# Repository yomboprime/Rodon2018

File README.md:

# Rodon2018
Open source wheeled robot.

This project will hold schematics, designs and code for a complete robot.

The robot electronics consist of an SBC (Raspberry-like board) and a Arduino/ESP/STM32-like board.

The main goal of the project is to create software for a wheeled robot suited for a diversity of common controller boards and hardware, i.e. Raspberry-like boards, microcontroller boards, and "Arduino modules". The particular hardware used in the project may differ from yours.

The libre tools used are: Kicad for the electronics, Freecad and Blender for the 3D designs, Inkscape for 2D artwork, and your favourite manner of editing code.

## Documentation

Please read the [project documentation](doc/1_DocumentationMain.md)

## Project phases history

- ✔️ Design MicrocontrollerBoard: Kicad design for the microcontroller board (Atmega1284P-PU)
- ➡️ Ordering and waiting for PCB arrival.
- Test MicrocontrollerBoard with motors.
- Do code a basic software & firmware.
- Keep growing functionality

## Acknowledgements

The small Lidar sensor code is based on the Adafruit VL53L0X Library, which is also MIT Licensed:

### Adafruit VL53L0X Library 

This is a library for the Adafruit VL53L0X time-of-flight breakout:
  * https://www.adafruit.com/products/3317
 
Check out the links above for our tutorials and wiring diagrams. This chip uses I2C to communicate

Adafruit invests time and resources providing this open source code, please support Adafruit and open-source hardware by purchasing products from Adafruit!

Written by Limor Fried/Ladyada for Adafruit Industries.
MIT license, all text above must be included in any redistribution

## License

MIT Licensed, see LICENSE file.

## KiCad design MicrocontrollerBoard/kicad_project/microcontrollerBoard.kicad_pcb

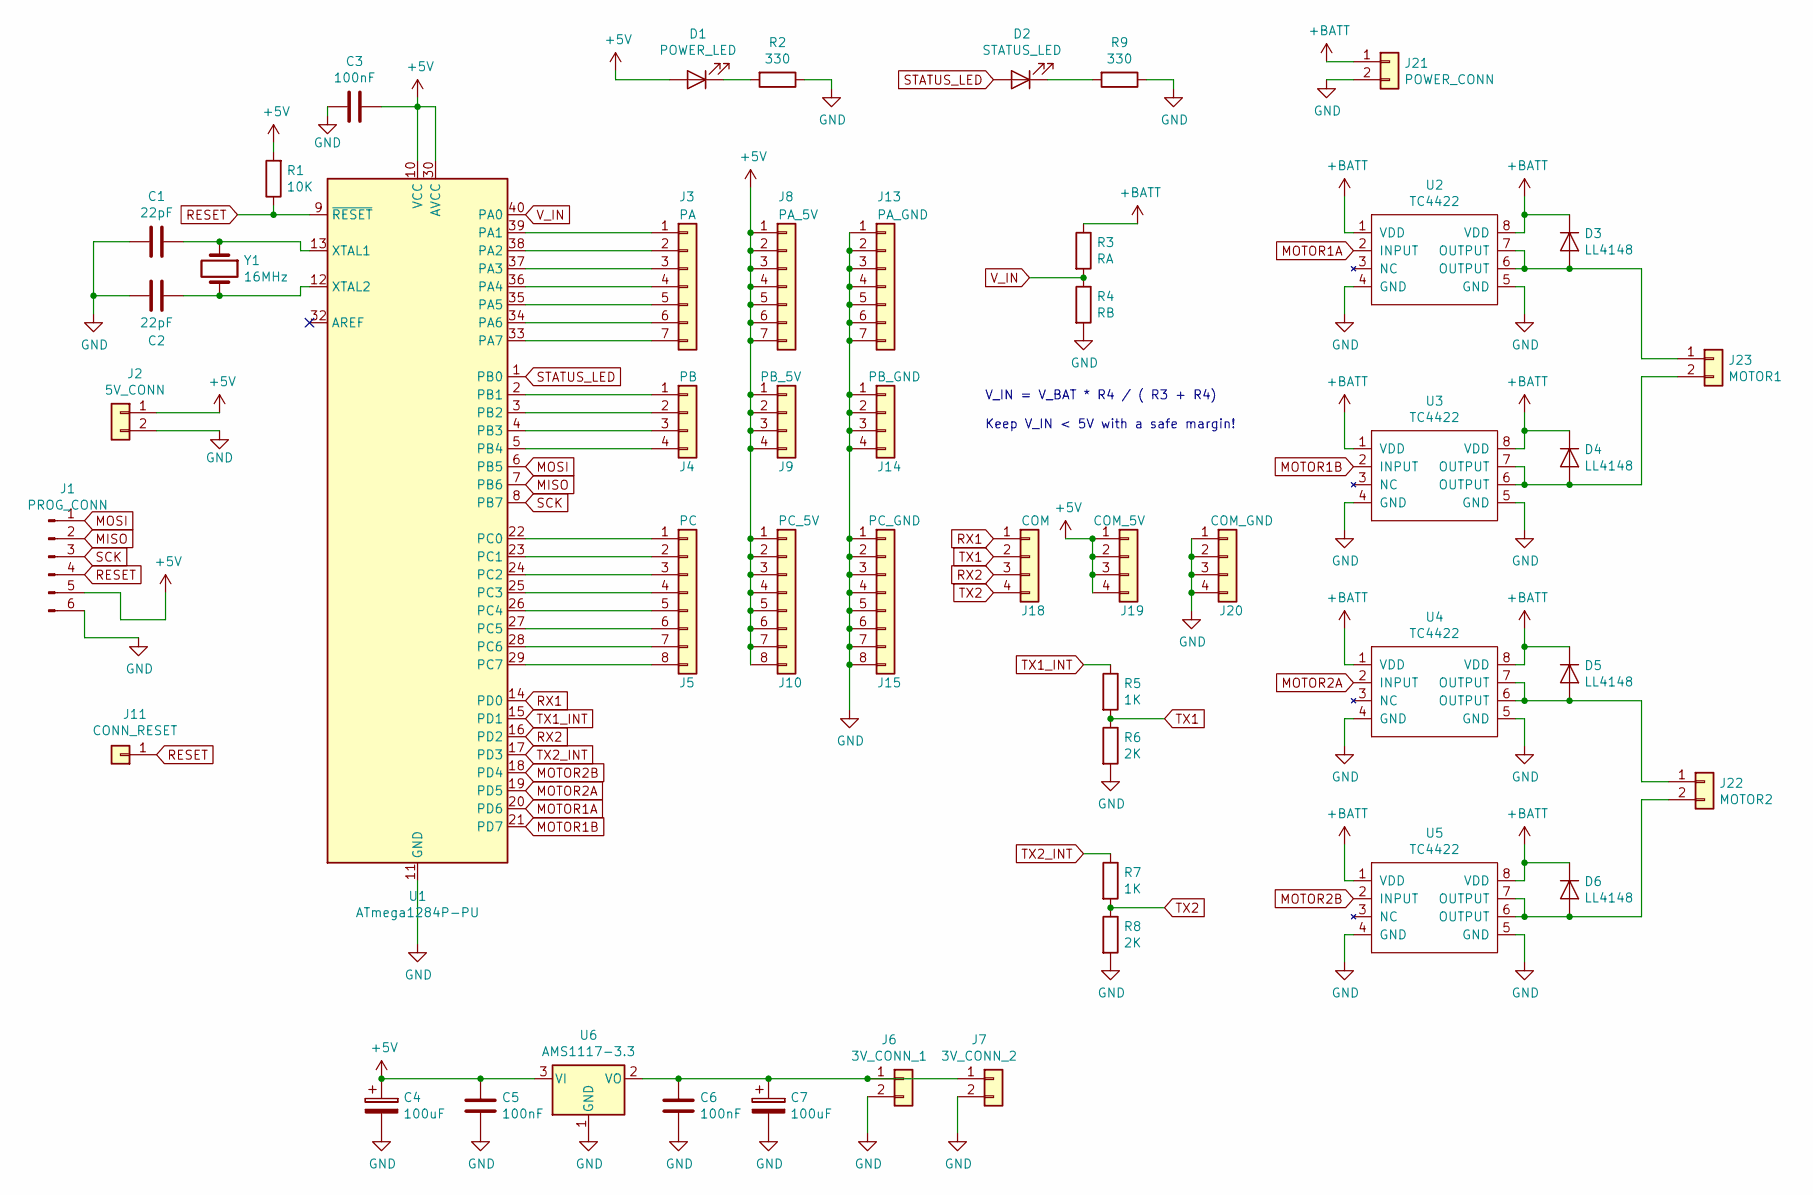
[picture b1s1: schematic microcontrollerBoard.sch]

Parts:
C1, C2: 22pF; C_0805_2012Metric_Pad1.15x1.40mm_HandSolder
C3: 100nF; C_0805_2012Metric_Pad1.15x1.40mm_HandSolder
C4, C7: 100uF; CP_Radial_D5.0mm_P2.50mm
C5, C6: 100nF; C_0603_1608Metric_Pad1.05x0.95mm_HandSolder
D1: POWER_LED; D_0805_2012Metric_Pad1.15x1.40mm_HandSolder
D2: STATUS_LED; D_0805_2012Metric_Pad1.15x1.40mm_HandSolder
D3, D4, D5, D6: LL4148; D_SOD-110
J1: PROG_CONN; PinHeader_1x06_P2.54mm_Vertical
J2: 5V_CONN; PinHeader_1x02_P2.54mm_Vertical
J3: PA; PinHeader_1x07_P2.54mm_Vertical
J4: PB; PinHeader_1x04_P2.54mm_Vertical
J5: PC; PinHeader_1x08_P2.54mm_Vertical
J6: 3V_CONN_1; PinHeader_1x02_P2.54mm_Vertical
J7: 3V_CONN_2; PinHeader_1x02_P2.54mm_Vertical
J8: PA_5V; PinHeader_1x07_P2.54mm_Vertical
J9: PB_5V; PinHeader_1x04_P2.54mm_Vertical
J10: PC_5V; PinHeader_1x08_P2.54mm_Vertical
J11: CONN_RESET; PinHeader_1x01_P2.54mm_Vertical
J13: PA_GND; PinHeader_1x07_P2.54mm_Vertical
J14: PB_GND; PinHeader_1x04_P2.54mm_Vertical
J15: PC_GND; PinHeader_1x08_P2.54mm_Vertical
J18: COM; PinHeader_1x04_P2.54mm_Vertical
J19: COM_5V; PinHeader_1x04_P2.54mm_Vertical
J20: COM_GND; PinHeader_1x04_P2.54mm_Vertical
J21: POWER_CONN; PinHeader_1x02_P2.54mm_Vertical
J22: MOTOR2; PinHeader_1x02_P2.54mm_Vertical
J23: MOTOR1; PinHeader_1x02_P2.54mm_Vertical
R1: 10K; R_0805_2012Metric_Pad1.15x1.40mm_HandSolder
R2, R9: 330; R_0805_2012Metric_Pad1.15x1.40mm_HandSolder
R3: RA; R_0805_2012Metric_Pad1.15x1.40mm_HandSolder
R4: RB; R_0805_2012Metric_Pad1.15x1.40mm_HandSolder
R5, R7: 1K; R_0805_2012Metric_Pad1.15x1.40mm_HandSolder
R6, R8: 2K; R_0805_2012Metric_Pad1.15x1.40mm_HandSolder
U1: ATmega1284P-PU; DIP-40_W15.24mm
U2, U3, U4, U5: TC4422; DIP-8_W7.62mm_Socket_LongPads
U6: AMS1117-3.3; SOT-223-3_TabPin2
Y1: 16MHz; Crystal_HC49-U_Vertical

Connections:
+5V: C3.1, C4.1, C5.1, D1.2 (A), J1.5, J2.1, J8.1, J8.2, J8.3, J8.4, J8.5, J8.6, J8.7, J9.1, J9.2, J9.3, J9.4, J10.1, J10.2, J10.3, J10.4, J10.5, J10.6, J10.7, J10.8, J19.1, J19.2, J19.3, J19.4, R1.2, U1.10 (VCC), U1.30 (AVCC), U6.3 (VI)
+BATT: D3.1 (K), D4.1 (K), D5.1 (K), D6.1 (K), J21.1, R3.1, U2.1 (VDD), U2.8 (VDD), U3.1 (VDD), U3.8 (VDD), U4.1 (VDD), U4.8 (VDD), U5.1 (VDD), U5.8 (VDD)
GND: C1.2, C2.2, C3.2, C4.2, C5.2, C6.2, C7.2, J1.6, J2.2, J6.2, J7.2, J13.1, J13.2, J13.3, J13.4, J13.5, J13.6, J13.7, J14.1, J14.2, J14.3, J14.4, J15.1, J15.2, J15.3, J15.4, J15.5, J15.6, J15.7, J15.8, J20.1, J20.2, J20.3, J20.4, J21.2, R2.1, R4.2, R6.2, R8.2, R9.1, U1.11 (GND), U1.31 (GND), U2.4 (GND), U2.5 (GND), U3.4 (GND), U3.5 (GND), U4.4 (GND), U4.5 (GND), U5.4 (GND), U5.5 (GND), U6.1 (GND)
MISO: J1.2, U1.7 (PB6)
MOSI: J1.1, U1.6 (PB5)
MOTOR1A: U1.20 (PD6), U2.2 (INPUT)
MOTOR1B: U1.21 (PD7), U3.2 (INPUT)
MOTOR2A: U1.19 (PD5), U4.2 (INPUT)
MOTOR2B: U1.18 (PD4), U5.2 (INPUT)
unnamed: C1.1, U1.13 (XTAL1), Y1.1
unnamed: C2.1, U1.12 (XTAL2), Y1.2
unnamed: C6.1, C7.1, J6.1, J7.1, U6.2 (VO)
unnamed: D1.1 (K), R2.2
unnamed: D2.1 (K), R9.2
unnamed: D3.2 (A), J23.1, U2.6 (OUTPUT), U2.7 (OUTPUT)
unnamed: D4.2 (A), J23.2, U3.6 (OUTPUT), U3.7 (OUTPUT)
unnamed: D5.2 (A), J22.1, U4.6 (OUTPUT), U4.7 (OUTPUT)
unnamed: D6.2 (A), J22.2, U5.6 (OUTPUT), U5.7 (OUTPUT)
unnamed: J3.1, U1.39 (PA1)
unnamed: J3.2, U1.38 (PA2)
unnamed: J3.3, U1.37 (PA3)
unnamed: J3.4, U1.36 (PA4)
unnamed: J3.5, U1.35 (PA5)
unnamed: J3.6, U1.34 (PA6)
unnamed: J3.7, U1.33 (PA7)
unnamed: J4.1, U1.2 (PB1)
unnamed: J4.2, U1.3 (PB2)
unnamed: J4.3, U1.4 (PB3)
unnamed: J4.4, U1.5 (PB4)
unnamed: J5.1, U1.22 (PC0)
unnamed: J5.2, U1.23 (PC1)
unnamed: J5.3, U1.24 (PC2)
unnamed: J5.4, U1.25 (PC3)
unnamed: J5.5, U1.26 (PC4)
unnamed: J5.6, U1.27 (PC5)
unnamed: J5.7, U1.28 (PC6)
unnamed: J5.8, U1.29 (PC7)
RESET: J1.4, J11.1, R1.1, U1.9 (~RESET)
RX1: J18.1, U1.14 (PD0)
RX2: J18.3, U1.16 (PD2)
SCK: J1.3, U1.8 (PB7)
STATUS_LED: D2.2 (A), U1.1 (PB0)
TX1: J18.2, R5.2, R6.1
TX1_INT: R5.1, U1.15 (PD1)
TX2: J18.4, R7.2, R8.1
TX2_INT: R7.1, U1.17 (PD3)
V_IN: R3.2, R4.1, U1.40 (PA0)

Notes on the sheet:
V_IN = V_BAT * R4 / ( R3 + R4) Keep V_IN < 5V with a safe margin!

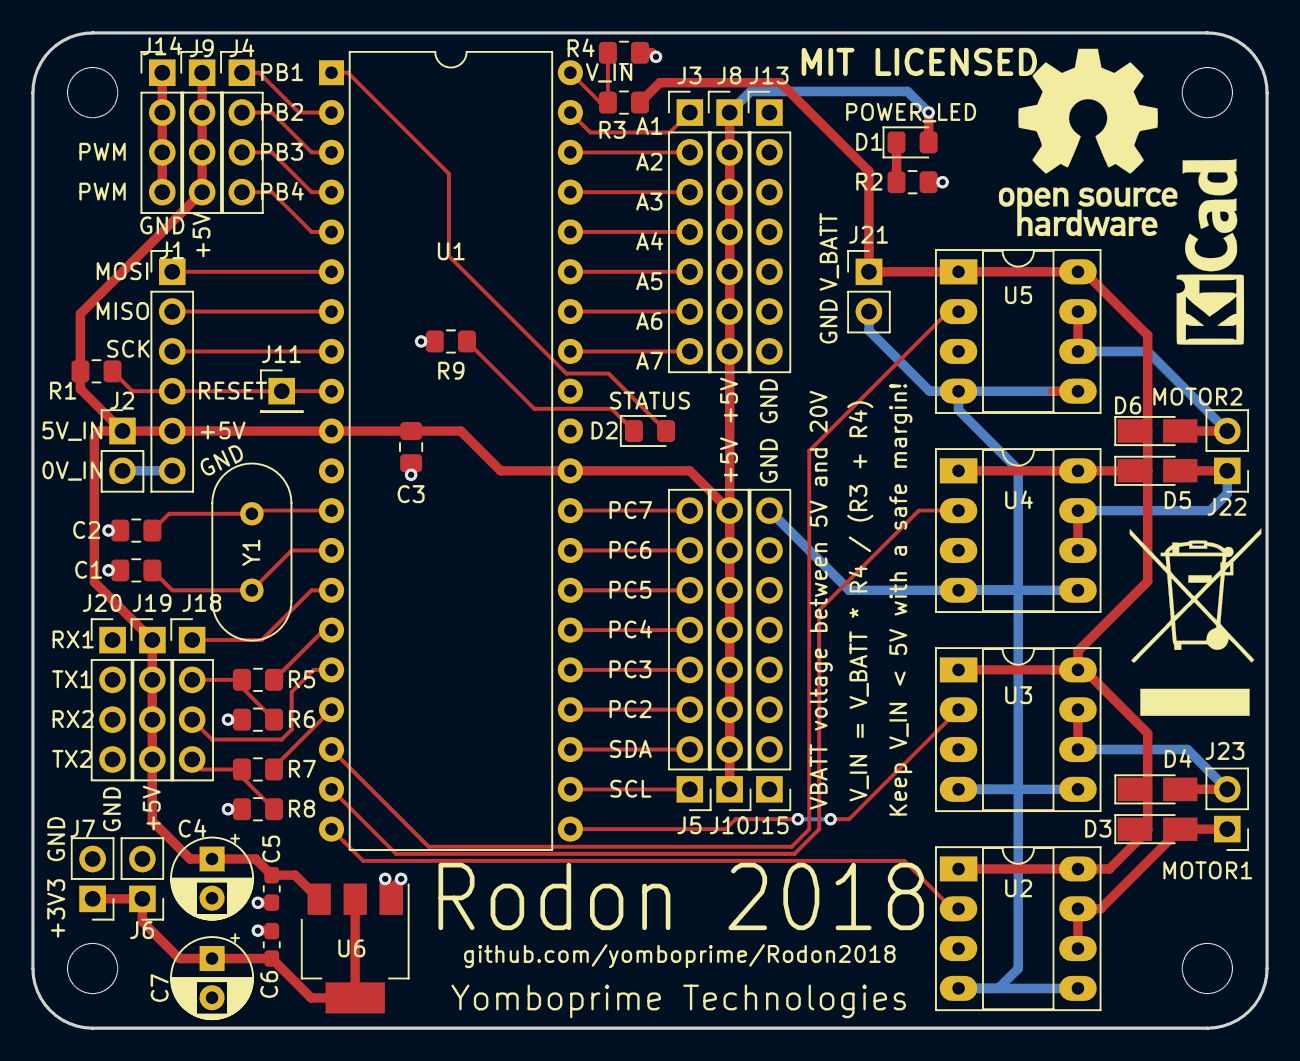
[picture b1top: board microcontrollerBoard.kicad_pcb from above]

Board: 2 copper layers, 78.7 x 63.5 mm, 49 parts (0 on the bottom side), 47 nets.

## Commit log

2018-10-18 Microcontroller kicad board design.
2018-10-18 Update README bis
2018-10-22 Changed TC4422 footprints to non socket so the 3D model has the chips.
2018-10-22 Update screenshot
2018-11-06 Microcontroller bord: Fixed PWM lines not going to uc's PWM pins. Added 3V3 regulator.
2018-11-06 Updated screenshot
2018-11-06 Microcontroller board: Some minor fixes.
2018-11-06 Microcontroller board: Updated gerbers.
2018-11-06 uC board: Renamed board project/directory
2018-11-06 uC board: Added resistors to MISO, brought out a RESET pin, minor fixes.
2018-11-07 uC board: V_IN is no longer exposed. Better power routing.
2018-11-07 Modify .gitignore
2018-11-07 Add documentation
2018-11-07 Fix readme
2018-11-07 Small doc correction
2018-11-07 uC board: better ground plane connection.
2018-11-07 More docs
2018-11-08 Revised ICSP header, motor diodes.
2018-11-08 Update gerbers
2018-11-10 uC board: Add motor diodes values (LL4148)
